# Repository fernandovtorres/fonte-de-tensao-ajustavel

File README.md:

# Fonte de tensão ajustável

*Projeto para a disciplina Eletronica para Computação - SSC0180*

# Integrantes do Grupo

- Nicholas Eiti Dan - 14600749
- João Gabriel Araújo de Bastos - 15462633
- Matheus Vieira Fernandes - 14615993
- Fernando Valentim Torres - 15452340

# Sobre o Projeto

Neste trabalho, projetamos uma fonte de tensão regulável 3v a 12v. Para isso, utilizamos a voltagem alternada de 127v 60hz vinda da tomada e transformamos em voltagem contínua utilizando um transformador e um circuito retificador feito com diodos.

# Tabela dos componentes
| Componente               | Quantidade | Custo por unidade |
|--------------------------|------------|-------|
|Transformador 24.2v        |1          |emprestado|
| Resistor 100 ohms, 2 watts|  2        |  1.70 |
| Transistor NPN            | 4         |  1.55 |
| Resistor 100 ohms, 0.25 watt | 6      |  0.08 |
| Capacitor 840 µF         | 1          |  5.20 |
| Diodos (ponte retificadora) | 4       |  0.20 |
| Zener 13V                | 1          |  0.50 |
| Zener 3.9V (queda de 2.4V) | 1        |  0.37 |
| Potenciômetro 10 kOhms   | 1          |  7.00 |
| LED vermelho             | 1          |  0.50 |
| Protoboard 830 pontos    | 2          | 12.26 |
| Jumpers                  | 27         |  0.70 |
|Resistor 4.7k ohms        |2           |  0.58 |  
|Resistor 2.2k ohms        |1           |  0.60 |
|Resistor 3.3k ohms        |1           |  0.39 |
|Resistor 1k ohms          |1           |  0.59 |
|Resistor 10k ohms         |1           |  0.46 |
|----- | **`TOTAL: 57`** | **`Preço Total: R$ 32,68`** |

# Informações sobre os componentes
- **transformador**: tem o papel de reduzir a voltagem de 127v vinda de uma fonte de corrente alternada (a tomada) para 24.2v, ainda alternada.
- **ponte de diodo**: a ponte de diodo é um arranjo de 4 diodos dispostos de uma forma com que a corrente alternada se tranforme em contínua
- **capacitor**: armazena carga no circuito durante os ciclos, liberando corrente quando a tensão provinda da fonte for menor do que a tensão interna do capacitor. Com base em um cálculo de 4% de ripple, chegamos próximos ao valor comercial de 820uF
- **diodo zener**: quando a voltagem passa de 13v, ele mantém esse valor como máximo em seus terminais, porém quando a voltagem é menor do que 13v, ele não conduz, logo não interfere
- **potenciômetro**: é um resistor regulável que será usado como o controle da tensão final.
- **transistor**: amplifica a corrente com base na resistência do potenciometro.
- **resistores**: utilizado em diversoss momentos no circuito, possui a função de limitar a corrente, o que garante uma certa segurança para os outros componentes do circuito.
- **led**: tem como função indicar quando a voltagem atingir 5 volts na parte final do circuito. de modo geral, não interfere nos valores obtidos no circuito, servindo unicamente como indicação da voltagem e corrente ajustáveis.

# Cálculos

### Antes do transformador:

$$ \ V_{\text{tomada}} = 127\ V \quad \Rightarrow \quad V_{\text{pico da tomada}} = 127 \cdot \sqrt{2} \approx 179,6\ V \ $$

### Após o transformador:

$$ \ V_0\ \text{pico} \approx 179,6 \cdot 0,1533 \approx 26,1\ V \ $$

### Depois da ponte retificadora:

$$ \ V_1\ \text{pico} \approx 26,1 - 2,6 \approx 23,5\ V \ $$

### Buscando a capacitância mínima para um ripple de no máximo 10%:

$$ \ R_{\text{eq}} \approx 230Ω \ $$

$$\ V_{\text{ripple}} = \frac{V_{\text{cc}}}{f \cdot C \cdot R_{\text{eq}}} \quad \Rightarrow \quad 2,35 \geq \frac{V_1\ \text{pico}}{120 \cdot C \cdot R_{\text{eq}}} \ $$

$$ \ \quad 2,35 \geq \frac{23,5}{120 \cdot C \cdot 230} \ $$

$$ \ C \geq \frac{23,5}{120 \cdot 2,35 \cdot 230} \approx 362\ \mu F \ $$

### Com um capacitor de 820µF, é possível obter um ripple de:

$$ \ \frac{10^6}{120 \cdot 820 \cdot 230} \approx 4\\% \ $$

# Imagem do Falstad

[Link para o falstad](https://tinyurl.com/2gezskvp)

# PCB no Eagle

# Esquemático no Eagle

# Foto do Projeto

# Vídeos

https://github.com/fernandovtorres/fonte-de-tensao-ajustavel/assets/54219097/06e4c6fe-193a-48ef-a1b3-73d7a6c7bd2a

[Video Explicativo](https://youtu.be/Dz2hcll39sc)

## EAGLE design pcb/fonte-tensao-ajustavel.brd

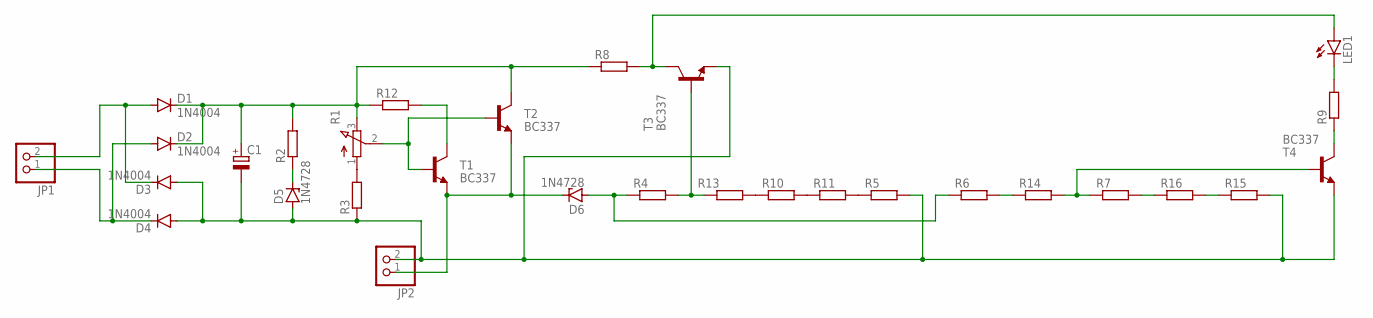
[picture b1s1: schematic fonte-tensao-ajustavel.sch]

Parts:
C1: CPOL-EUE5-10.5; E5-10,5
D1, D2, D3, D4: 1N4004; DO41-10
D5, D6: 1N4728; DO41Z10
JP1, JP2: PINHD-1X2; 1X02
LED1: LED5MM
R1: 3RP/1610N
R2, R3, R4, R5, R6, R7, R8, R9, R10, R11, R13, R14, R15, R16: R-EU_0204/7; 0204/7
R12: R-EU_0414/15; 0414/15
T1, T2, T3, T4: BC337; TO92

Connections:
unnamed: D1.A, D3.C, JP1.2
unnamed: D2.A, D4.C, JP1.1
unnamed: R5.1, R11.2
unnamed: C1.-, D3.A, D4.A, D5.A, JP2.2, R3.1, R5.2, R15.2, T3.1 (E), T4.1 (E)
unnamed: D5.C, R2.1
unnamed: R1.1 (A), R3.2
unnamed: D6.C, JP2.1, T1.1 (E), T2.1 (E)
unnamed: R1.2 (S), T1.2 (B), T2.2 (B)
unnamed: C1.+, D1.C, D2.C, R1.3 (E), R2.2, R8.1, R12.1, T2.3 (C)
unnamed: D6.A, R4.1, R6.1
unnamed: R4.2, R13.1, T3.2 (B)
unnamed: R7.1, R14.2, T4.2 (B)
unnamed: LED1.K (C), R9.2
unnamed: R9.1, T4.3 (C)
unnamed: LED1.A, R8.2, T3.3 (C)
unnamed: R12.2, T1.3 (C)
unnamed: R10.2, R11.1
unnamed: R10.1, R13.2
unnamed: R6.2, R14.1
unnamed: R7.2, R16.1
unnamed: R15.1, R16.2

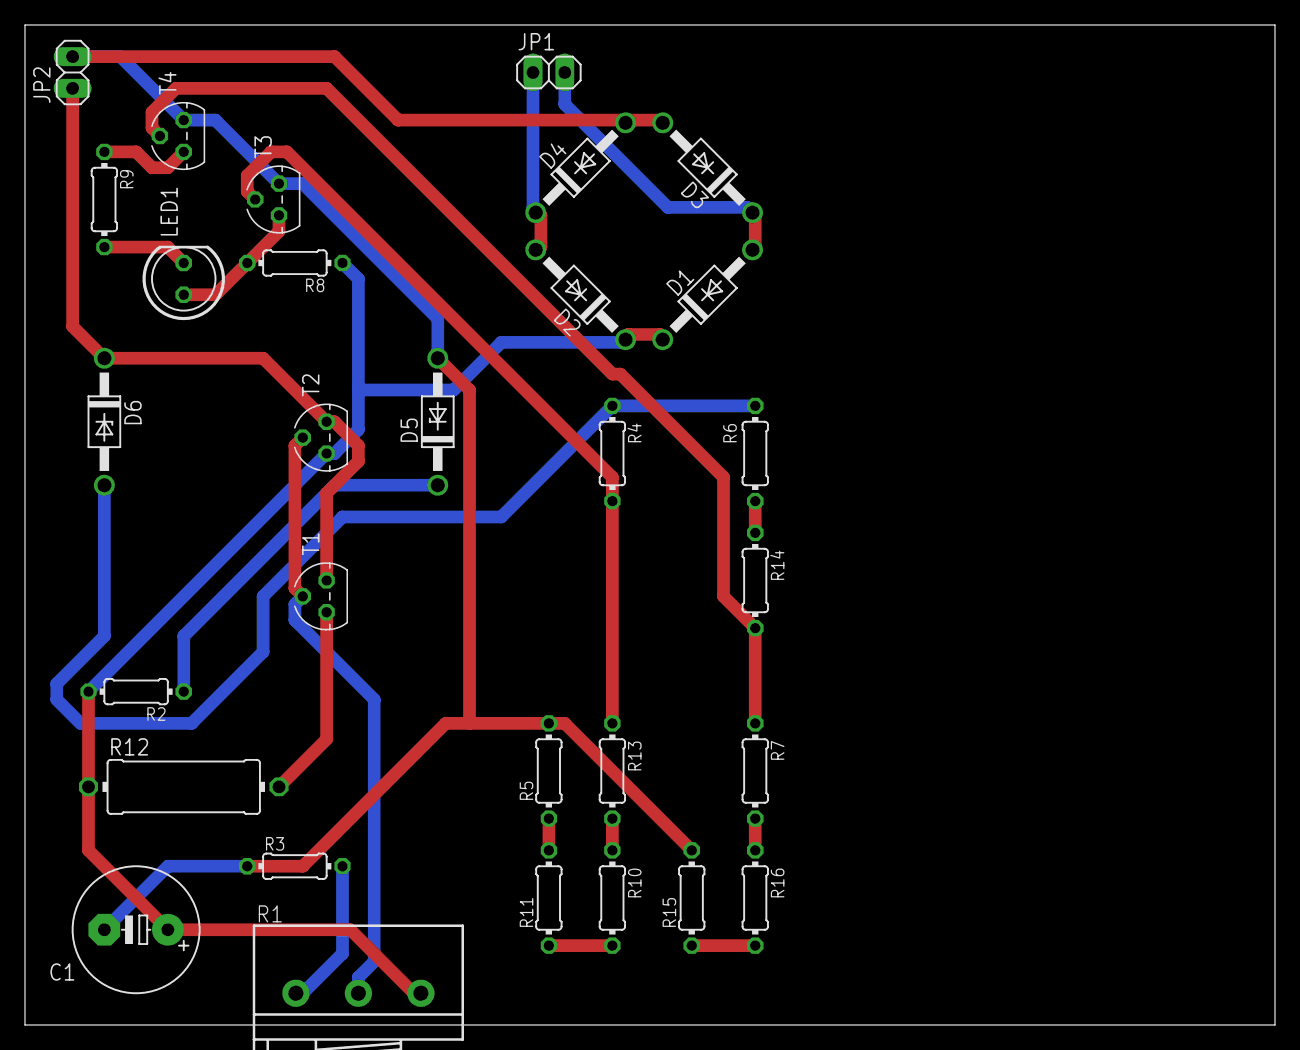
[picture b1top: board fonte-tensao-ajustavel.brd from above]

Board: 2 copper layers, 100.0 x 80.0 mm, 30 parts (0 on the bottom side), 21 nets.

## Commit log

2024-06-29 Adicionar arquivos da PCB criados no Eagle
2024-12-06 só que não sei o que
